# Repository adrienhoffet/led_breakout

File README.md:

# led_breakout
Small pcb to hold the led for lipmann presenter

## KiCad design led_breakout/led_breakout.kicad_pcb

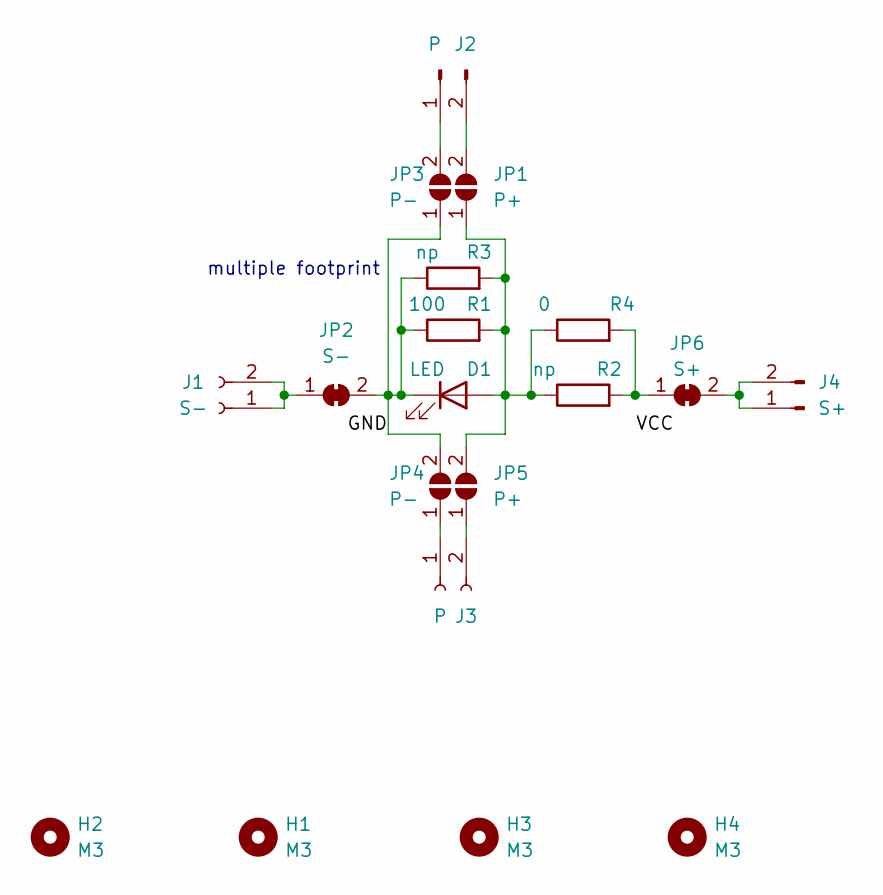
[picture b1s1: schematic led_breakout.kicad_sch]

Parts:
D1: LED; LED_Cree-XH
H1, H2, H3, H4: M3; MountingHole_3.2mm_M3_ISO7380
J1: S-; PinSocket_1x02_P2.54mm_Horizontal
J2: P; PinHeader_1x02_P2.54mm_Horizontal
J3: P; PinSocket_1x02_P2.54mm_Horizontal
J4: S+; PinHeader_1x02_P2.54mm_Horizontal
JP1, JP5: P+; SolderJumper-2_P1.3mm_Open_RoundedPad1.0x1.5mm
JP2: S-; SolderJumper-2_P1.3mm_Bridged_RoundedPad1.0x1.5mm
JP3, JP4: P-; SolderJumper-2_P1.3mm_Open_RoundedPad1.0x1.5mm
JP6: S+; SolderJumper-2_P1.3mm_Bridged_RoundedPad1.0x1.5mm
R1: 100; R_2512_6332Metric
R2: np; R_2512_6332Metric
R3: np; R_0805_2012Metric
R4: 0; R_0805_2012Metric

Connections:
/GND: D1.1 (K), JP2.2 (B), JP3.1 (A), JP4.2 (B), R1.1, R3.1
unnamed: D1.2 (A), JP1.1 (A), JP5.2 (B), R1.2, R2.1, R3.2, R4.1
unnamed: J1.1, J1.2, JP2.1 (A)
unnamed: J2.1, JP3.2 (B)
unnamed: J2.2, JP1.2 (B)
unnamed: J3.1, JP4.1 (A)
unnamed: J3.2, JP5.1 (A)
unnamed: J4.1, J4.2, JP6.2 (B)
unnamed: JP6.1 (A), R2.2, R4.2

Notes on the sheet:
multiple footprint

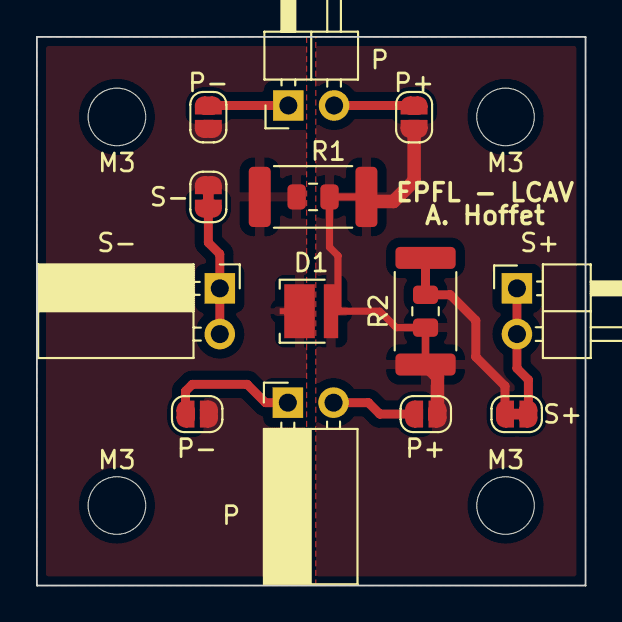
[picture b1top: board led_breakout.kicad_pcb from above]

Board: 2 copper layers, 30.5 x 30.5 mm, 19 parts (0 on the bottom side), 9 nets.

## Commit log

2022-04-26 Update PCB and edit schematics
2022-04-26 Edit Schematic and add Parts Number
2022-04-26 Fix gitignore
2022-06-23 update resistor value
2022-07-06 Fix PCB errors after first assembly
2022-07-06 Add references for external components
